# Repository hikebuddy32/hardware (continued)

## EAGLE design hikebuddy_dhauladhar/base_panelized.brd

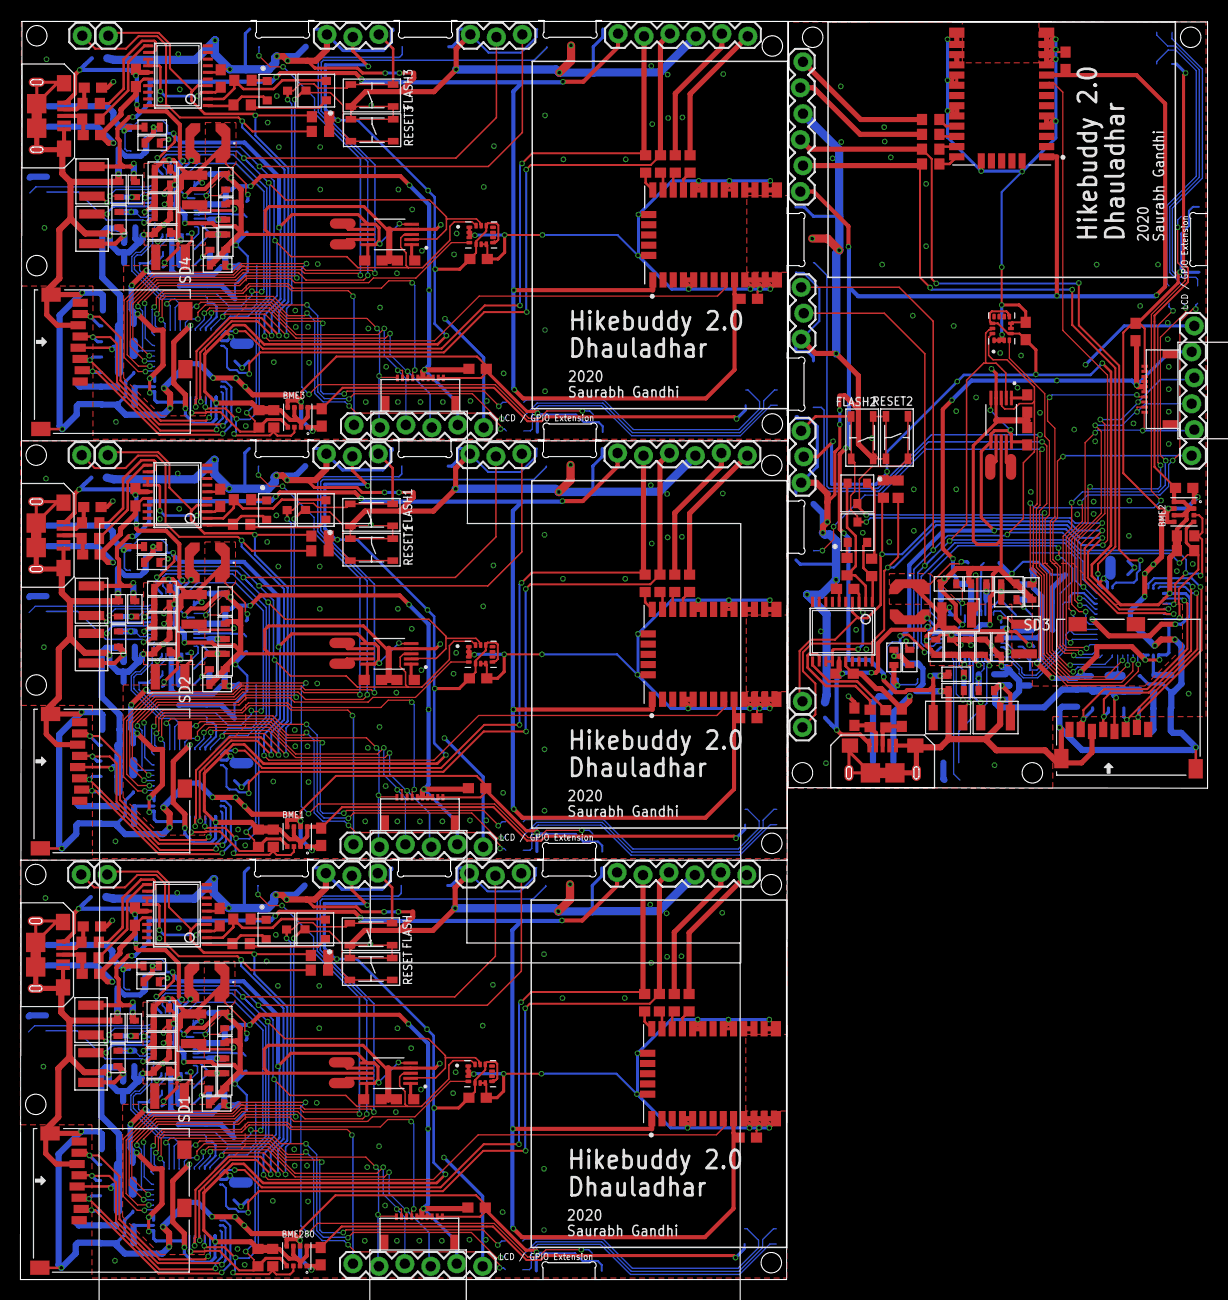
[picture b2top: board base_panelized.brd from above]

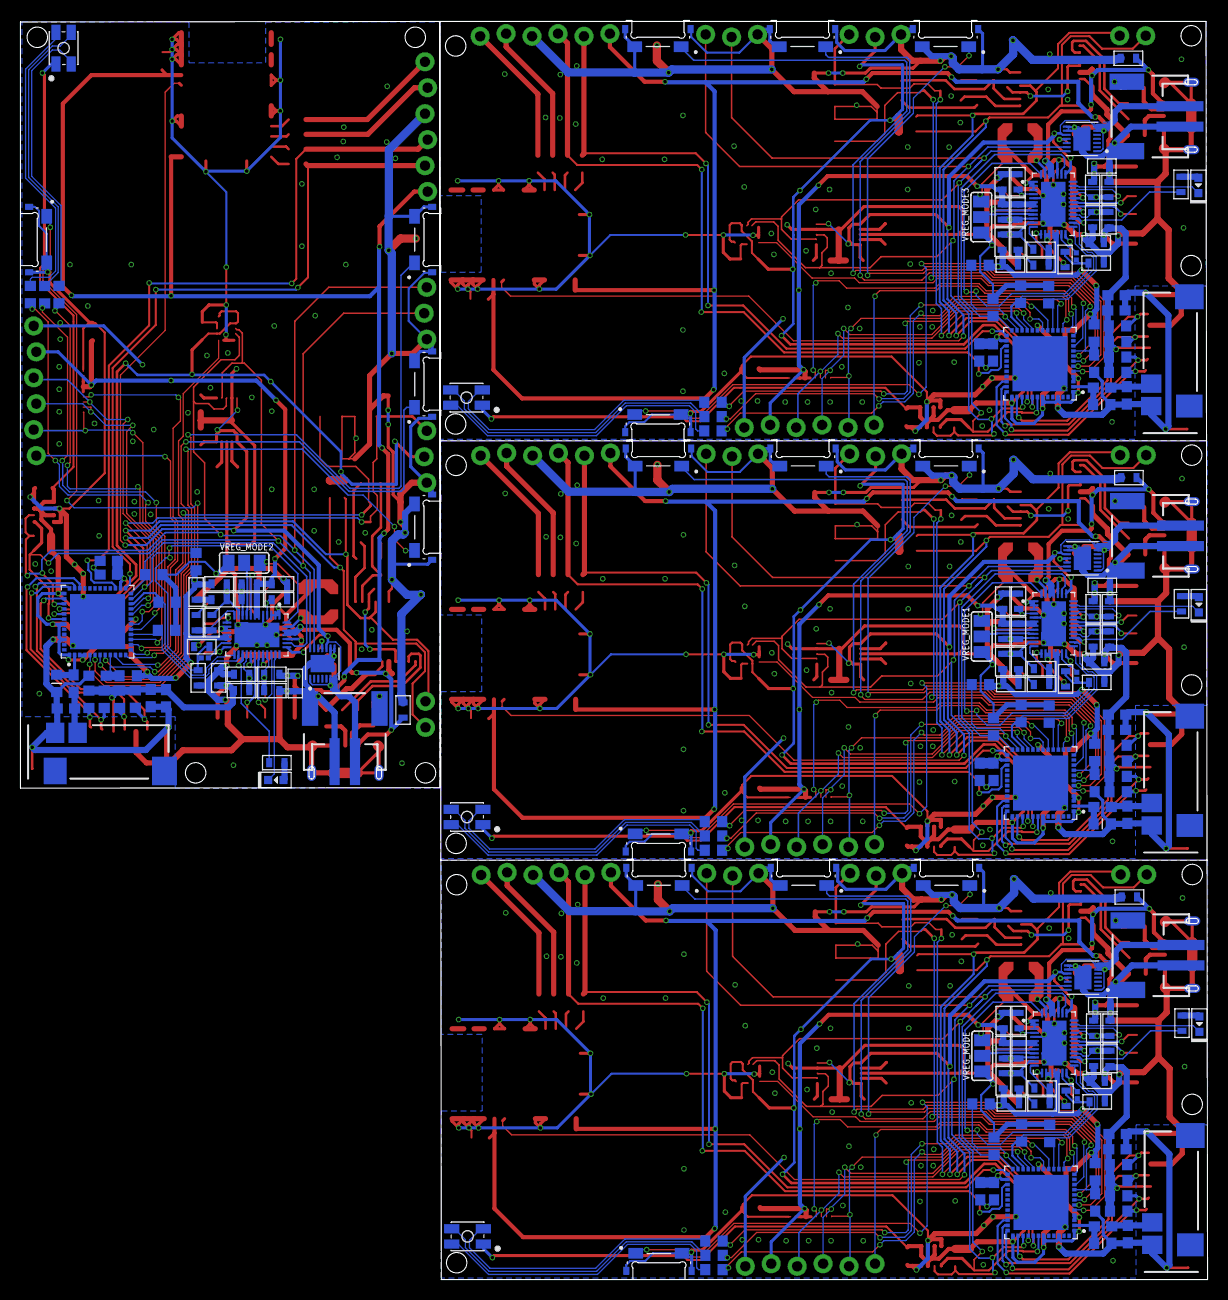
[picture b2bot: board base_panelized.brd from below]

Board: 2 copper layers, 116.2 x 123.2 mm, 456 parts (212 on the bottom side), 324 nets.

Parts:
ANT, ANT1, ANT2, ANT3: PRO-OB-440; PRO-OB-440_1
BATTERY1, BATTERY2, BATTERY3, BATTERY4: S2B-PH-SM4-TB(LF)(SN); JST-2-SMD
BME1, BME2, BME3, BME280: BME280; PSON65P250X250X100-8N
C1, C2, C22, C39, C75, C76, C112, C113: 4.7pF; C0603
C3, C4, C10, C14, C15, C20, C35, C40, C41, C45, C46, C49, C66, C73, C77, C78, C82, C83, C86, C103, C110, C114, C115, C119, C120, C123, C140, C147: 0.1uF; C0603
C5, C6, C42, C43, C79, C80, C116, C117: 47pF; C0603
C7, C8, C9, C16, C21, C23, C24, C27, C28, C38, C44, C47, C48, C53, C55, C58, C59, C71, C72, C74, C81, C84, C85, C90, C92, C95, C96, C108, C109, C111, C118, C121, C122, C127, C129, C132, C133, C145, C146, C148: 10uF; C0603
C11, C12, C29, C30, C50, C51, C60, C61, C87, C88, C97, C98, C124, C125, C134, C135: 22uF; C0603
C13, C18, C33, C52, C54, C64, C89, C91, C101, C126, C128, C138: 10pF; C0603
C17, C19, C36, C37, C67, C68, C69, C70, C104, C105, C106, C107, C141, C142, C143, C144: 4.7uF; C0603
C25, C26, C56, C57, C93, C94, C130, C131: 1uF; C0603
C31, C62, C99, C136: 33pF; C0603
C32, C63, C100, C137: 330pF; C0603
C34, C65, C102, C139: 0.47uF; C0603
D1, D3, D6, D8: MF-LED-0603-RED; LED0603
D2, D4, D5, D7: MF-LED-3228-RGB; PLCC4
ESP32-PICO-D1, ESP32-PICO-D2, ESP32-PICO-D3, ESP32-PICO-D4: ESP32-PICO-D4; PQFN50P700X700X104-49N
FLASH, FLASH1, FLASH2, FLASH3: MF-SW-TACT-4.2MM; TACT4.2MM
FT1, FT2, FT3, FT231: FT231XS; TSSOP20
J1, J10, J18, J26: MF-CON-MICROUSB-RIGHT; MICROUSB-RIGHT
J2, J9, J17, J25: GPS Port; 1X06_LOCK
J3, J4, J11, J12, J19, J20, J27, J28: 1X03_LOCK
J5, J13, J21, J29: SOLDER_PAD_2
J6, J7, J14, J15, J22, J23, J30, J31: 1X01
J8, J16, J24, J32: 1X06_LOCK
L1, L7, L13, L19: 30Ω/1.8A; L0603
L2, L8, L14, L20: 3.3uH; INDP_LPS4018-472MRB
L3, L5, L9, L11, L15, L17, L21, L23: 2.2uH; L1210
L4, L6, L10, L12, L16, L18, L22, L24: 4.7uH; L1210
R1, R2, R5, R6, R12, R13, R14, R30, R31, R32, R33, R36, R39, R43, R44, R47, R48, R49, R53, R73, R74, R75, R77, R78, R81, R82, R85, R86, R87, R91, R111, R112, R113, R115, R116, R119, R120, R123, R124, R125, R129, R149, R150, R151: 10k; R0603
R3, R4, R34, R35, R79, R80, R117, R118: 27; R0603
R7, R37, R38, R54, R55, R60, R92, R93, R98, R130, R131, R136: 2K; R0603
R8, R61, R99, R137: 3K; R0603
R9, R62, R100, R138: 560K; R0603
R10, R11, R40, R41, R42, R45, R46, R50, R51, R52, R83, R84, R88, R89, R90, R121, R122, R126, R127, R128: 1k; R0603
R15, R17, R18, R19, R56, R57, R58, R59, R94, R95, R96, R97, R132, R133, R134, R135: 100; R0603
R16, R21, R64, R76, R102, R114, R140, R152: 1K; R0603
R20, R63, R101, R139: 100K; R0603
R22, R24, R27, R65, R67, R70, R103, R105, R108, R141, R143, R146: 220K; R0603
R23, R25, R26, R66, R68, R69, R104, R106, R107, R142, R144, R145: 680K; R0603
R28, R71, R109, R147: 121K; R0603
R29, R72, R110, R148: 15K; R0603
RESET, RESET1, RESET2, RESET3: MF-SW-TACT-4.2MM; TACT4.2MM
S1, S2, S3, S4, S5, S6, S7, S8, S9, S10, S11, S12, S13, S14, S15, S16: EVQ-P4HB3B; SW_EVQ-P4HB3B
SD1, SD2, SD3, SD4: MF-MICROSD
TP1, TP2, TP3, TP4, TP5, TP6, TP7, TP8: TEST-POINT2; PAD.02X.02
U1, U9, U15, U21: LTC3586EUFE-1#PBF; QFN40P600X400X80-39N
U2, U10, U16, U22: MAX17260SETD+; SON40P300X300X80-15N
U3, U4, U7, U8, U13, U14, U19, U20: MF-DSC-SOT233-MMBT3904; SOT-23-3
U5, U11, U17, U23: DRV2605LTDGSRQ1; SOP50P490X110-10N
U6, U12, U18, U24: BMX160; PQFN50P250X300X100-14N
U$1, U$2, U$3, U$5: 51441-1093; FH12-10S-0.5SH
UBLOX_GPS, UBLOX_GPS1, UBLOX_GPS2, UBLOX_GPS3: CAM-M8C-0; LCC100P960X1400X210-31N
VREG_MODE, VREG_MODE1, VREG_MODE2, VREG_MODE3: VREG MODE; SJ_2

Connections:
3V3_GPS: C13.P$1, C16.P$2, C17.1, J2.6, L4.P$1, R23.P$1, UBLOX_GPS.1, UBLOX_GPS.9
3V3_GPS1: C52.P$1, C53.P$2, C69.1, J9.6, L10.P$1, R66.P$1, UBLOX_GPS1.1, UBLOX_GPS1.9
3V3_GPS2: C89.P$1, C90.P$2, C106.1, J17.6, L16.P$1, R104.P$1, UBLOX_GPS2.1, UBLOX_GPS2.9
3V3_GPS3: C126.P$1, C127.P$2, C143.1, J25.6, L22.P$1, R142.P$1, UBLOX_GPS3.1, UBLOX_GPS3.9
3V3_SDC: C14.1, C15.1, C18.P$1, C24.P$1, L6.P$2, R12.2, R13.2, R14.2, R25.P$1, R43.2, SD1.PIN4
3V3_SDC1: C45.1, C46.1, C54.P$1, C55.P$1, L12.P$2, R47.2, R48.2, R49.2, R53.2, R68.P$1, SD2.PIN4
3V3_SDC2: C82.1, C83.1, C91.P$1, C92.P$1, L18.P$2, R85.2, R86.2, R87.2, R91.2, R106.P$1, SD3.PIN4
3V3_SDC3: C119.1, C120.1, C128.P$1, C129.P$1, L24.P$2, R123.2, R124.2, R125.2, R129.2, R144.P$1, SD4.PIN4
BMX_INT: ESP32-PICO-D4.10, U6.4
BMX_INT1: ESP32-PICO-D1.10, U12.4
BMX_INT2: ESP32-PICO-D2.10, U18.4
BMX_INT3: ESP32-PICO-D3.10, U24.4
D+: C6.1, J1.3, R4.1
D+1: C43.1, J10.3, R35.1
D+2: C80.1, J18.3, R80.1
D+3: C117.1, J26.3, R118.1
D-: C5.1, J1.2, R3.1
D-1: C42.1, J10.2, R34.1
D-2: C79.1, J18.2, R79.1
D-3: C116.1, J26.2, R117.1
EN_GPS: ESP32-PICO-D4.16, R31.2, U1.21
EN_GPS1: ESP32-PICO-D1.16, R74.2, U9.21
EN_GPS2: ESP32-PICO-D2.16, R112.2, U15.21
EN_GPS3: ESP32-PICO-D3.16, R150.2, U21.21
EN_LCD: ESP32-PICO-D4.24, R36.2, U1.33
EN_LCD1: ESP32-PICO-D1.24, R75.2, U9.33
EN_LCD2: ESP32-PICO-D2.24, R113.2, U15.33
EN_LCD3: ESP32-PICO-D3.24, R151.2, U21.33
EN_SDC: ESP32-PICO-D4.22, R30.2, U1.20
EN_SDC1: ESP32-PICO-D1.22, R73.2, U9.20
EN_SDC2: ESP32-PICO-D2.22, R111.2, U15.20
EN_SDC3: ESP32-PICO-D3.22, R149.2, U21.20
ESP_EN: C3.2, ESP32-PICO-D4.9, R1.1, RESET.P$1, RESET.P$2, U4.P$3
ESP_EN1: C40.2, ESP32-PICO-D1.9, R32.1, RESET1.P$1, RESET1.P$2, U8.P$3
ESP_EN2: C77.2, ESP32-PICO-D2.9, R77.1, RESET2.P$1, RESET2.P$2, U14.P$3
ESP_EN3: C114.2, ESP32-PICO-D3.9, R115.1, RESET3.P$1, RESET3.P$2, U20.P$3
ESP_FLASH: ESP32-PICO-D4.23, FLASH.P$1, FLASH.P$2, J4.3, R2.1, U3.P$3
ESP_FLASH1: ESP32-PICO-D1.23, FLASH1.P$1, FLASH1.P$2, J12.3, R33.1, U7.P$3
ESP_FLASH2: ESP32-PICO-D2.23, FLASH2.P$1, FLASH2.P$2, J20.3, R78.1, U13.P$3
ESP_FLASH3: ESP32-PICO-D3.23, FLASH3.P$1, FLASH3.P$2, J28.3, R116.1, U19.P$3
ESP_RX: ESP32-PICO-D4.40, FT231.20, J6.1, R11.1
ESP_RX1: ESP32-PICO-D1.40, FT1.20, J14.1, R46.1
ESP_RX2: ESP32-PICO-D2.40, FT2.20, J22.1, R84.1
ESP_RX3: ESP32-PICO-D3.40, FT3.20, J30.1, R122.1
ESP_TX: ESP32-PICO-D4.41, FT231.4, J7.1, R10.1
ESP_TX1: ESP32-PICO-D1.41, FT1.4, J15.1, R45.1
ESP_TX2: ESP32-PICO-D2.41, FT2.4, J23.1, R83.1
ESP_TX3: ESP32-PICO-D3.41, FT3.4, J31.1, R121.1
GND: ANT.1, BATTERY1.1, BATTERY1.NC1, BATTERY1.NC2, BME280.1, BME280.5, BME280.7, C2.1, C3.1, C4.2, C5.2, C6.2, C7.2, C8.1, C9.P$2, C10.P$1, C12.P$1, C14.2, C15.2, C16.P$1, C17.2, C19.1, C20.P$1, C21.2, C23.2, C24.P$2, C25.P$1, C26.P$1, C27.P$1, C28.P$1, C29.P$1, C30.P$2, C34.P$1, C35.P$1, C36.2, C37.1, C38.1, ESP32-PICO-D4.49, FLASH.P$3, FLASH.P$4, FT231.6, FT231.16, J1.5, J1.S1, J1.S2, J1.S3, J1.S4, J1.S5, J1.S6, J2.3, J3.1, J4.1, J8.1, L1.2, R7.P$1, R8.P$1, R20.P$1, R22.P$2, R24.P$2, R27.P$1, R30.1, R31.1, R36.1, RESET.P$3, RESET.P$4, S1.2, S1.3, S1.4, S2.2, S2.3, S2.4, S3.2, S3.3, S3.4, S4.2, S4.3, S4.4, SD1.G0, SD1.G1, SD1.PIN6, U1.5, U1.39, U2.8, U2.9, U2.15, U5.4, U5.8, U6.1, U6.2, U6.3, U6.6, U6.7, U$5.VSS, U$5.VSSA, UBLOX_GPS.4, UBLOX_GPS.5, UBLOX_GPS.10, UBLOX_GPS.11, UBLOX_GPS.12, UBLOX_GPS.13, UBLOX_GPS.14, UBLOX_GPS.15, UBLOX_GPS.18, UBLOX_GPS.19, UBLOX_GPS.21, UBLOX_GPS.22, UBLOX_GPS.27, UBLOX_GPS.31, VREG_MODE.1
GND1: ANT1.1, BATTERY2.1, BATTERY2.NC1, BATTERY2.NC2, BME1.1, BME1.5, BME1.7, C39.1, C40.1, C41.2, C42.2, C43.2, C44.2, C45.2, C46.2, C47.2, C48.P$2, C49.P$1, C51.P$1, C53.P$1, C55.P$2, C56.P$1, C57.P$1, C58.P$1, C59.P$1, C60.P$1, C61.P$2, C65.P$1, C66.P$1, C67.2, C68.1, C69.2, C70.1, C71.1, C72.1, C73.P$1, C74.2, ESP32-PICO-D1.49, FLASH1.P$3, FLASH1.P$4, FT1.6, FT1.16, J9.3, J10.5, J10.S1, J10.S2, J10.S3, J10.S4, J10.S5, J10.S6, J11.1, J12.1, J16.1, L7.2, R60.P$1, R61.P$1, R63.P$1, R65.P$2, R67.P$2, R70.P$1, R73.1, R74.1, R75.1, RESET1.P$3, RESET1.P$4, S5.2, S5.3, S5.4, S6.2, S6.3, S6.4, S7.2, S7.3, S7.4, S8.2, S8.3, S8.4, SD2.G0, SD2.G1, SD2.PIN6, U9.5, U9.39, U10.8, U10.9, U10.15, U11.4, U11.8, U12.1, U12.2, U12.3, U12.6, U12.7, U$1.VSS, U$1.VSSA, UBLOX_GPS1.4, UBLOX_GPS1.5, UBLOX_GPS1.10, UBLOX_GPS1.11, UBLOX_GPS1.12, UBLOX_GPS1.13, UBLOX_GPS1.14, UBLOX_GPS1.15, UBLOX_GPS1.18, UBLOX_GPS1.19, UBLOX_GPS1.21, UBLOX_GPS1.22, UBLOX_GPS1.27, UBLOX_GPS1.31, VREG_MODE1.1
GND2: ANT3.1, BATTERY4.1, BATTERY4.NC1, BATTERY4.NC2, BME3.1, BME3.5, BME3.7, C113.1, C114.1, C115.2, C116.2, C117.2, C118.2, C119.2, C120.2, C121.2, C122.P$2, C123.P$1, C125.P$1, C127.P$1, C129.P$2, C130.P$1, C131.P$1, C132.P$1, C133.P$1, C134.P$1, C135.P$2, C139.P$1, C140.P$1, C141.2, C142.1, C143.2, C144.1, C145.1, C146.1, C147.P$1, C148.2, ESP32-PICO-D3.49, FLASH3.P$3, FLASH3.P$4, FT3.6, FT3.16, J25.3, J26.5, J26.S1, J26.S2, J26.S3, J26.S4, J26.S5, J26.S6, J27.1, J28.1, J32.1, L19.2, R136.P$1, R137.P$1, R139.P$1, R141.P$2, R143.P$2, R146.P$1, R149.1, R150.1, R151.1, RESET3.P$3, RESET3.P$4, S13.2, S13.3, S13.4, S14.2, S14.3, S14.4, S15.2, S15.3, S15.4, S16.2, S16.3, S16.4, SD4.G0, SD4.G1, SD4.PIN6, U21.5, U21.39, U22.8, U22.9, U22.15, U23.4, U23.8, U24.1, U24.2, U24.3, U24.6, U24.7, U$3.VSS, U$3.VSSA, UBLOX_GPS3.4, UBLOX_GPS3.5, UBLOX_GPS3.10, UBLOX_GPS3.11, UBLOX_GPS3.12, UBLOX_GPS3.13, UBLOX_GPS3.14, UBLOX_GPS3.15, UBLOX_GPS3.18, UBLOX_GPS3.19, UBLOX_GPS3.21, UBLOX_GPS3.22, UBLOX_GPS3.27, UBLOX_GPS3.31, VREG_MODE3.1
GND3: ANT2.1, BATTERY3.1, BATTERY3.NC1, BATTERY3.NC2, BME2.1, BME2.5, BME2.7, C76.1, C77.1, C78.2, C79.2, C80.2, C81.2, C82.2, C83.2, C84.2, C85.P$2, C86.P$1, C88.P$1, C90.P$1, C92.P$2, C93.P$1, C94.P$1, C95.P$1, C96.P$1, C97.P$1, C98.P$2, C102.P$1, C103.P$1, C104.2, C105.1, C106.2, C107.1, C108.1, C109.1, C110.P$1, C111.2, ESP32-PICO-D2.49, FLASH2.P$3, FLASH2.P$4, FT2.6, FT2.16, J17.3, J18.5, J18.S1, J18.S2, J18.S3, J18.S4, J18.S5, J18.S6, J19.1, J20.1, J24.1, L13.2, R98.P$1, R99.P$1, R101.P$1, R103.P$2, R105.P$2, R108.P$1, R111.1, R112.1, R113.1, RESET2.P$3, RESET2.P$4, S9.2, S9.3, S9.4, S10.2, S10.3, S10.4, S11.2, S11.3, S11.4, S12.2, S12.3, S12.4, SD3.G0, SD3.G1, SD3.PIN6, U15.5, U15.39, U16.8, U16.9, U16.15, U17.4, U17.8, U18.1, U18.2, U18.3, U18.6, U18.7, U$2.VSS, U$2.VSSA, UBLOX_GPS2.4, UBLOX_GPS2.5, UBLOX_GPS2.10, UBLOX_GPS2.11, UBLOX_GPS2.12, UBLOX_GPS2.13, UBLOX_GPS2.14, UBLOX_GPS2.15, UBLOX_GPS2.18, UBLOX_GPS2.19, UBLOX_GPS2.21, UBLOX_GPS2.22, UBLOX_GPS2.27, UBLOX_GPS2.31, VREG_MODE2.1
GPIO_EXT: ESP32-PICO-D4.13, J8.6
GPIO_EXT1: ESP32-PICO-D1.13, J16.6
GPIO_EXT2: ESP32-PICO-D2.13, J24.6
GPIO_EXT3: ESP32-PICO-D3.13, J32.6
GPS_RESET: J2.1, R18.2
GPS_RESET1: J9.1, R58.2
GPS_RESET2: J17.1, R96.2
GPS_RESET3: J25.1, R134.2
GPS_RX: ESP32-PICO-D4.25, J2.5, R17.2
GPS_RX1: ESP32-PICO-D1.25, J9.5, R57.2
GPS_RX2: ESP32-PICO-D2.25, J17.5, R95.2
GPS_RX3: ESP32-PICO-D3.25, J25.5, R133.2
GPS_SAFEBOOT: J2.2, R19.2
GPS_SAFEBOOT1: J9.2, R59.2
GPS_SAFEBOOT2: J17.2, R97.2
GPS_SAFEBOOT3: J25.2, R135.2
GPS_TX: ESP32-PICO-D4.27, J2.4, R15.1
GPS_TX1: ESP32-PICO-D1.27, J9.4, R56.1
GPS_TX2: ESP32-PICO-D2.27, J17.4, R94.1
GPS_TX3: ESP32-PICO-D3.27, J25.4, R132.1
I2C_SCL: BME280.4, ESP32-PICO-D4.42, J3.2, R37.1, U2.14, U5.2, U6.13
I2C_SCL1: BME1.4, ESP32-PICO-D1.42, J11.2, R54.1, U10.14, U11.2, U12.13
I2C_SCL2: BME2.4, ESP32-PICO-D2.42, J19.2, R92.1, U16.14, U17.2, U18.13
I2C_SCL3: BME3.4, ESP32-PICO-D3.42, J27.2, R130.1, U22.14, U23.2, U24.13
I2C_SDA: BME280.3, ESP32-PICO-D4.39, J3.3, R38.1, U2.13, U5.3, U6.14
I2C_SDA1: BME1.3, ESP32-PICO-D1.39, J11.3, R55.1, U10.13, U11.3, U12.14
I2C_SDA2: BME2.3, ESP32-PICO-D2.39, J19.3, R93.1, U16.13, U17.3, U18.14
I2C_SDA3: BME3.3, ESP32-PICO-D3.39, J27.3, R131.1, U22.13, U23.3, U24.14
JUMPER: U1.9, VREG_MODE.2
JUMPER1: U9.9, VREG_MODE1.2
JUMPER2: U15.9, VREG_MODE2.2
JUMPER3: U21.9, VREG_MODE3.2
LCD_CLK: ESP32-PICO-D4.17, J8.5, U$5.SCLK
LCD_CLK1: ESP32-PICO-D1.17, J16.5, U$1.SCLK
LCD_CLK2: ESP32-PICO-D2.17, J24.5, U$2.SCLK
LCD_CLK3: ESP32-PICO-D3.17, J32.5, U$3.SCLK
LCD_CS: ESP32-PICO-D4.21, J8.3, U$5.SCS
LCD_CS1: ESP32-PICO-D1.21, J16.3, U$1.SCS
LCD_CS2: ESP32-PICO-D2.21, J24.3, U$2.SCS
LCD_CS3: ESP32-PICO-D3.21, J32.3, U$3.SCS
LCD_EXTCOMM: ESP32-PICO-D4.12, U$5.EXTCOMIN
LCD_EXTCOMM1: ESP32-PICO-D1.12, U$1.EXTCOMIN
LCD_EXTCOMM2: ESP32-PICO-D2.12, U$2.EXTCOMIN
LCD_EXTCOMM3: ESP32-PICO-D3.12, U$3.EXTCOMIN
LCD_MOSI: ESP32-PICO-D4.20, J8.4, U$5.SI
LCD_MOSI1: ESP32-PICO-D1.20, J16.4, U$1.SI
LCD_MOSI2: ESP32-PICO-D2.20, J24.4, U$2.SI
LCD_MOSI3: ESP32-PICO-D3.20, J32.4, U$3.SI
LED1: ESP32-PICO-D4.18, R40.1
LED2: ESP32-PICO-D4.15, R41.1
LED3: ESP32-PICO-D4.14, R42.1
LED4: ESP32-PICO-D1.18, R50.1
LED5: ESP32-PICO-D1.15, R51.1
LED6: ESP32-PICO-D1.14, R52.1
LED7: ESP32-PICO-D2.18, R88.1
LED8: ESP32-PICO-D2.15, R89.1
LED9: ESP32-PICO-D2.14, R90.1
LED10: ESP32-PICO-D3.18, R126.1
LED11: ESP32-PICO-D3.15, R127.1
LED12: ESP32-PICO-D3.14, R128.1
unnamed: C1.1, ESP32-PICO-D4.2, L1.1
unnamed: ANT.2, C1.2, C2.2
unnamed: R5.2, U3.P$1
unnamed: R6.2, U4.P$1
unnamed: C4.1, FT231.3, FT231.13, FT231.14
unnamed: FT231.12, R3.2
unnamed: FT231.11, R4.2
unnamed: FT231.2, R5.1, U4.P$2
unnamed: FT231.1, R6.1, U3.P$2
unnamed: R7.P$2, U1.29
unnamed: C10.P$2, R8.P$2, U1.4
unnamed: C11.P$1, R9.P$1, R20.P$2, U1.10
unnamed: L3.P$2, U1.13
unnamed: C31.P$1, C32.P$1, C33.P$1, R26.P$1, R27.P$2, U1.11
unnamed: L2.2, U1.37
unnamed: D1.CATHODE, U1.30
unnamed: D1.ANODE, R21.P$1
unnamed: L3.P$1, U1.19
unnamed: TP2.P$1, U1.18
unnamed: L4.P$2, U1.26
unnamed: C13.P$2, R22.P$1, R23.P$2, U1.28
unnamed: L5.P$1, U1.8
unnamed: C22.1, ESP32-PICO-D1.2, L7.1
unnamed: C20.P$2, R16.P$2, TP1.P$1, U1.38
unnamed: ANT1.2, C22.2, C39.2
unnamed: C18.P$2, R24.P$1, R25.P$2, U1.23
unnamed: L6.P$1, U1.25
unnamed: D4.P$2, R40.2
unnamed: R15.2, UBLOX_GPS.25
unnamed: R17.1, UBLOX_GPS.26
unnamed: C31.P$2, R28.P$1
unnamed: D4.P$3, R42.2
unnamed: D4.P$4, R41.2
unnamed: UBLOX_GPS.16, UBLOX_GPS.17
unnamed: C41.1, FT1.3, FT1.13, FT1.14
unnamed: FT1.12, R34.2
unnamed: R18.1, UBLOX_GPS.23
unnamed: R19.1, UBLOX_GPS.24
unnamed: FT1.11, R35.2
unnamed: R39.2, U7.P$1
unnamed: C36.1, U5.1
unnamed: R44.2, U8.P$1
unnamed: C33.P$2, R29.P$2, U1.12
unnamed: C32.P$2, R29.P$1
unnamed: FT1.2, R39.1, U8.P$2
unnamed: FT1.1, R44.1, U7.P$2
unnamed: C34.P$2, U2.11
unnamed: D2.P$2, R50.2
unnamed: D2.P$4, R51.2
unnamed: J5.P$2, U5.9
unnamed: J5.P$1, U5.7
unnamed: D2.P$3, R52.2
unnamed: R56.2, UBLOX_GPS1.25
unnamed: R57.1, UBLOX_GPS1.26
unnamed: UBLOX_GPS1.16, UBLOX_GPS1.17
unnamed: R58.1, UBLOX_GPS1.23
unnamed: R59.1, UBLOX_GPS1.24
unnamed: R60.P$2, U9.29
unnamed: C49.P$2, R61.P$2, U9.4
unnamed: L8.2, U9.37
unnamed: D3.CATHODE, U9.30
unnamed: D3.ANODE, R64.P$1
unnamed: L9.P$2, U9.13
unnamed: L9.P$1, U9.19
unnamed: L10.P$2, U9.26
unnamed: C52.P$2, R65.P$1, R66.P$2, U9.28
unnamed: C54.P$2, R67.P$1, R68.P$2, U9.23
unnamed: L12.P$1, U9.25
unnamed: L11.P$1, U9.8
unnamed: C50.P$1, R62.P$1, R63.P$2, U9.10
unnamed: C62.P$1, C63.P$1, C64.P$1, R69.P$1, R70.P$2, U9.11
unnamed: C62.P$2, R71.P$1
unnamed: C64.P$2, R72.P$2, U9.12
unnamed: C63.P$2, R72.P$1
unnamed: C65.P$2, U10.11
unnamed: C67.1, U11.1
unnamed: J13.P$2, U11.9
unnamed: J13.P$1, U11.7
unnamed: C73.P$2, R76.P$2, TP3.P$1, U9.38
unnamed: TP4.P$1, U9.18
unnamed: C75.1, ESP32-PICO-D2.2, L13.1
unnamed: ANT2.2, C75.2, C76.2
unnamed: C78.1, FT2.3, FT2.13, FT2.14
unnamed: FT2.12, R79.2
unnamed: FT2.11, R80.2
unnamed: R81.2, U13.P$1
unnamed: R82.2, U14.P$1
unnamed: FT2.2, R81.1, U14.P$2
unnamed: FT2.1, R82.1, U13.P$2
unnamed: D5.P$2, R88.2
unnamed: D5.P$4, R89.2
unnamed: D5.P$3, R90.2
unnamed: R94.2, UBLOX_GPS2.25
unnamed: R95.1, UBLOX_GPS2.26
unnamed: UBLOX_GPS2.16, UBLOX_GPS2.17
unnamed: R96.1, UBLOX_GPS2.23
unnamed: R97.1, UBLOX_GPS2.24
unnamed: R98.P$2, U15.29
unnamed: C86.P$2, R99.P$2, U15.4
unnamed: L14.2, U15.37
unnamed: D6.CATHODE, U15.30
unnamed: D6.ANODE, R102.P$1
unnamed: L15.P$2, U15.13
unnamed: L15.P$1, U15.19
unnamed: L16.P$2, U15.26
unnamed: C89.P$2, R103.P$1, R104.P$2, U15.28
unnamed: C91.P$2, R105.P$1, R106.P$2, U15.23
unnamed: L18.P$1, U15.25
unnamed: L17.P$1, U15.8
unnamed: C87.P$1, R100.P$1, R101.P$2, U15.10
unnamed: C99.P$1, C100.P$1, C101.P$1, R107.P$1, R108.P$2, U15.11
unnamed: C99.P$2, R109.P$1
unnamed: C101.P$2, R110.P$2, U15.12
unnamed: C100.P$2, R110.P$1
unnamed: C102.P$2, U16.11
unnamed: C104.1, U17.1
unnamed: J21.P$2, U17.9
unnamed: J21.P$1, U17.7
unnamed: C110.P$2, R114.P$2, TP5.P$1, U15.38
unnamed: TP6.P$1, U15.18
unnamed: C112.1, ESP32-PICO-D3.2, L19.1
unnamed: ANT3.2, C112.2, C113.2
unnamed: C115.1, FT3.3, FT3.13, FT3.14
unnamed: FT3.12, R117.2
unnamed: FT3.11, R118.2
unnamed: R119.2, U19.P$1
unnamed: R120.2, U20.P$1
unnamed: FT3.2, R119.1, U20.P$2
unnamed: FT3.1, R120.1, U19.P$2
unnamed: D7.P$2, R126.2
unnamed: D7.P$4, R127.2
unnamed: D7.P$3, R128.2
unnamed: R132.2, UBLOX_GPS3.25
unnamed: R133.1, UBLOX_GPS3.26
unnamed: UBLOX_GPS3.16, UBLOX_GPS3.17
unnamed: R134.1, UBLOX_GPS3.23
unnamed: R135.1, UBLOX_GPS3.24
unnamed: R136.P$2, U21.29
unnamed: C123.P$2, R137.P$2, U21.4
unnamed: L20.2, U21.37
unnamed: D8.CATHODE, U21.30
unnamed: D8.ANODE, R140.P$1
unnamed: L21.P$2, U21.13
unnamed: L21.P$1, U21.19
unnamed: L22.P$2, U21.26
unnamed: C126.P$2, R141.P$1, R142.P$2, U21.28
unnamed: C128.P$2, R143.P$1, R144.P$2, U21.23
unnamed: L24.P$1, U21.25
unnamed: L23.P$1, U21.8
unnamed: C124.P$1, R138.P$1, R139.P$2, U21.10
unnamed: C136.P$1, C137.P$1, C138.P$1, R145.P$1, R146.P$2, U21.11
unnamed: C136.P$2, R147.P$1
unnamed: C138.P$2, R148.P$2, U21.12
unnamed: C137.P$2, R148.P$1
unnamed: C139.P$2, U22.11
unnamed: C141.1, U23.1
unnamed: J29.P$2, U23.9
unnamed: J29.P$1, U23.7
unnamed: C147.P$2, R152.P$2, TP7.P$1, U21.38
unnamed: TP8.P$1, U21.18
SD_CLK: ESP32-PICO-D4.35, R14.1, SD1.PIN5
SD_CLK1: ESP32-PICO-D1.35, R49.1, SD2.PIN5
SD_CLK2: ESP32-PICO-D2.35, R87.1, SD3.PIN5
SD_CLK3: ESP32-PICO-D3.35, R125.1, SD4.PIN5
SD_CS: ESP32-PICO-D4.34, R12.1, SD1.PIN2
SD_CS1: ESP32-PICO-D1.34, R47.1, SD2.PIN2
SD_CS2: ESP32-PICO-D2.34, R85.1, SD3.PIN2
SD_CS3: ESP32-PICO-D3.34, R123.1, SD4.PIN2
SD_MISO: ESP32-PICO-D4.38, R43.1, SD1.PIN7
SD_MISO1: ESP32-PICO-D1.38, R53.1, SD2.PIN7
SD_MISO2: ESP32-PICO-D2.38, R91.1, SD3.PIN7
SD_MISO3: ESP32-PICO-D3.38, R129.1, SD4.PIN7
SD_MOSI: ESP32-PICO-D4.36, R13.1, SD1.PIN3
SD_MOSI1: ESP32-PICO-D1.36, R48.1, SD2.PIN3
SD_MOSI2: ESP32-PICO-D2.36, R86.1, SD3.PIN3
SD_MOSI3: ESP32-PICO-D3.36, R124.1, SD4.PIN3
SW1: ESP32-PICO-D4.5, S1.1
SW2: ESP32-PICO-D4.6, S4.1
SW3: ESP32-PICO-D4.7, S3.1
SW4: ESP32-PICO-D4.8, S2.1
SW5: ESP32-PICO-D1.5, S8.1
SW6: ESP32-PICO-D1.6, S7.1
SW7: ESP32-PICO-D1.7, S6.1
SW8: ESP32-PICO-D1.8, S5.1
SW9: ESP32-PICO-D2.5, S12.1
SW10: ESP32-PICO-D2.6, S11.1
SW11: ESP32-PICO-D2.7, S10.1
SW12: ESP32-PICO-D2.8, S9.1
SW13: ESP32-PICO-D3.5, S16.1
SW14: ESP32-PICO-D3.6, S15.1
SW15: ESP32-PICO-D3.7, S14.1
SW16: ESP32-PICO-D3.8, S13.1
VCC: BME280.2, BME280.6, BME280.8, C8.2, C21.1, C23.1, C30.P$1, C38.2, D4.P$1, ESP32-PICO-D4.1, ESP32-PICO-D4.3, ESP32-PICO-D4.4, ESP32-PICO-D4.19, ESP32-PICO-D4.26, ESP32-PICO-D4.37, ESP32-PICO-D4.43, ESP32-PICO-D4.46, J4.2, R1.2, R2.2, R10.2, R11.2, R26.P$2, R28.P$2, R37.2, R38.2, U1.16, U1.17, U6.5, U6.8, U6.12
VCC1: BME1.2, BME1.6, BME1.8, C47.1, C61.P$1, C71.2, C72.2, C74.1, D2.P$1, ESP32-PICO-D1.1, ESP32-PICO-D1.3, ESP32-PICO-D1.4, ESP32-PICO-D1.19, ESP32-PICO-D1.26, ESP32-PICO-D1.37, ESP32-PICO-D1.43, ESP32-PICO-D1.46, J12.2, R32.2, R33.2, R45.2, R46.2, R54.2, R55.2, R69.P$2, R71.P$2, U9.16, U9.17, U12.5, U12.8, U12.12
VCC2: BME2.2, BME2.6, BME2.8, C84.1, C98.P$1, C108.2, C109.2, C111.1, D5.P$1, ESP32-PICO-D2.1, ESP32-PICO-D2.3, ESP32-PICO-D2.4, ESP32-PICO-D2.19, ESP32-PICO-D2.26, ESP32-PICO-D2.37, ESP32-PICO-D2.43, ESP32-PICO-D2.46, J20.2, R77.2, R78.2, R83.2, R84.2, R92.2, R93.2, R107.P$2, R109.P$2, U15.16, U15.17, U18.5, U18.8, U18.12
VCC3: BME3.2, BME3.6, BME3.8, C121.1, C135.P$1, C145.2, C146.2, C148.1, D7.P$1, ESP32-PICO-D3.1, ESP32-PICO-D3.3, ESP32-PICO-D3.4, ESP32-PICO-D3.19, ESP32-PICO-D3.26, ESP32-PICO-D3.37, ESP32-PICO-D3.43, ESP32-PICO-D3.46, J28.2, R115.2, R116.2, R121.2, R122.2, R130.2, R131.2, R145.P$2, R147.P$2, U21.16, U21.17, U24.5, U24.8, U24.12
V_BAT: BATTERY1.2, C35.P$2, C37.2, U1.32, U2.1, U2.6, U2.7, U2.10, U5.5, U5.6, U5.10, UBLOX_GPS.8
V_BAT1: BATTERY2.2, C66.P$2, C68.2, U9.32, U10.1, U10.6, U10.7, U10.10, U11.5, U11.6, U11.10, UBLOX_GPS1.8
V_BAT2: BATTERY3.2, C103.P$2, C105.2, U15.32, U16.1, U16.6, U16.7, U16.10, U17.5, U17.6, U17.10, UBLOX_GPS2.8
V_BAT3: BATTERY4.2, C140.P$2, C142.2, U21.32, U22.1, U22.6, U22.7, U22.10, U23.5, U23.6, U23.10, UBLOX_GPS3.8
V_LCD: C11.P$2, C19.2, C29.P$2, J8.2, R9.P$2, U1.6, U1.7, U$5.DISP, U$5.EXTMODE, U$5.VDD, U$5.VDDA
V_LCD1: C50.P$2, C60.P$2, C70.2, J16.2, R62.P$2, U9.6, U9.7, U$1.DISP, U$1.EXTMODE, U$1.VDD, U$1.VDDA
V_LCD2: C87.P$2, C97.P$2, C107.2, J24.2, R100.P$2, U15.6, U15.7, U$2.DISP, U$2.EXTMODE, U$2.VDD, U$2.VDDA
V_LCD3: C124.P$2, C134.P$2, C144.2, J32.2, R138.P$2, U21.6, U21.7, U$3.DISP, U$3.EXTMODE, U$3.VDD, U$3.VDDA
V_REG: C12.P$2, C25.P$2, C26.P$2, C27.P$2, C28.P$2, L2.1, L5.P$2, R16.P$1, R21.P$2, U1.1, U1.2, U1.3, U1.14, U1.15, U1.22, U1.24, U1.27, U1.34, VREG_MODE.3
V_REG1: C51.P$2, C56.P$2, C57.P$2, C58.P$2, C59.P$2, L8.1, L11.P$2, R64.P$2, R76.P$1, U9.1, U9.2, U9.3, U9.14, U9.15, U9.22, U9.24, U9.27, U9.34, VREG_MODE1.3
V_REG2: C88.P$2, C93.P$2, C94.P$2, C95.P$2, C96.P$2, L14.1, L17.P$2, R102.P$2, R114.P$1, U15.1, U15.2, U15.3, U15.14, U15.15, U15.22, U15.24, U15.27, U15.34, VREG_MODE2.3
V_REG3: C125.P$2, C130.P$2, C131.P$2, C132.P$2, C133.P$2, L20.1, L23.P$2, R140.P$2, R152.P$1, U21.1, U21.2, U21.3, U21.14, U21.15, U21.22, U21.24, U21.27, U21.34, VREG_MODE3.3
V_USB: C7.1, C9.P$1, FT231.15, J1.1, U1.35, U1.36
V_USB1: C44.1, C48.P$1, FT1.15, J10.1, U9.35, U9.36
V_USB2: C81.1, C85.P$1, FT2.15, J18.1, U15.35, U15.36
V_USB3: C118.1, C122.P$1, FT3.15, J26.1, U21.35, U21.36

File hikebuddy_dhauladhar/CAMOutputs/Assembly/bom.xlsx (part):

Qty | Value | Device | Package | Parts | Description | AVAILABILITY | DESCRIPTION.1 | DIELECTRIC | DNP | HEIGHT | HOUSEPART | MANUFACTURER_NAME | MANUFACTURER_PART_NUMBER | MF | MOUSER_PART_NUMBER | MOUSER_PRICE-STOCK | MP | MPN | PACKAGE.1 | POPULARITY | POPULATE | PRICE | PROD_ID | RS_PART_NUMBER | RS_PRICE-STOCK | SF_ID | SPICEPREFIX | TOLERANCE | URL | VALUE.1 | VOLTAGE | WATTAGE | Column1
2 |  | CONN_01 | 1X01 | J6, J7 | Single connection point. Often used as Generic Header-pin footprint for 0.1 inc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 |  |  |  | 1
2 |  | CONN_03LOCK | 1X03_LOCK | J3, J4 | Multi connection point. Often used as Generic Header-pin footprint for 0.1 inch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 |  |  |  | 1
1 |  | CONN_06LOCK | 1X06_LOCK | J8 | Multi connection point. Often used as Generic Header-pin footprint for 0.1 inch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 |  |  |  | 1
1 | LTC3586EUFE-1#PBF | LTC3586EUFE-3#TRPBF | QFN40P600X400X80-39N | U1 | None | Unavailable | USB Power Manager 4.35V to 5.5V 38-Pin QFN EP T/R |  |  |  |  |  |  | Analog Devices |  |  | LTC3586EUFE |  | QFN -38 Analog Devices |  |  | None
4 | 0.1uF | 0.1UF-0603-25V-(+80/-20%) | C0603 | C3, C4, C14, C15 | 0.1ÂµF ceramic capacitors |  |  |  |  |  |  |  |  |  |  |  |  |  |  |  |  |  | CAP-00810 |  |  |  |  |  |  | 0.1uF
3 | 0.1uF | CAPACITOR_NP_0603 | C0603 | C10, C20, C35 | Library: MF_Passives |  |  |  |  |  |  |  |  |  |  |  |  |  |  |  | 1
1 | 0.47uF | CAPACITOR_NP_0603 | C0603 | C34 | Library: MF_Passives |  |  |  |  |  |  |  |  |  |  |  |  |  |  |  | 1
2 | 100 | 1KOHM-0603-1/10W-1% | R0603 | R18, R19 | 1kÎ© resistor |  |  |  | 1 |  |  |  |  |  |  |  |  |  |  |  |  |  | RES-07856 |  |  |  |  |  |  | 1k
2 | 100 | 1KOHM-0603-1/10W-1% | R0603 | R15, R17 | 1kÎ© resistor |  |  |  |  |  |  |  |  |  |  |  |  |  |  |  |  |  | RES-07856 |  |  |  |  |  |  | 1k
1 | 100K | RESISTOR_0603 | R0603 | R20 | Library: MF_Passives |  |  |  |  |  |  |  |  |  |  |  |  |  |  |  | 1
11 | 10k | 10KOHM-0603-1/10W-1% | R0603 | R1, R2, R5, R6, R12, R13, R14, R30, R31, R36, R43 | 10kÎ© resistor |  |  |  |  |  |  |  |  |  |  |  |  |  |  |  |  |  | RES-00824 |  |  |  |  |  |  | 10k
3 | 10pF | CAPACITOR_NP_0603 | C0603 | C13, C18, C33 | Library: MF_Passives |  |  |  |  |  |  |  |  |  |  |  |  |  |  |  | 1
2 | 10uF | 10UF-0603-6.3V-20% | C0603 | C21, C23 | 10.0ÂµF ceramic capacitors |  |  |  |  |  |  |  |  |  |  |  |  |  |  |  |  |  | CAP-11015 |  |  |  |  |  |  | 10uF
1 | 10uF | 2.2UF-0603-10V-20% | C0603 | C7 | 2.2ÂµF ceramic capacitors |  |  |  |  |  |  |  |  |  |  |  |  |  |  |  |  |  | CAP-07888 |  |  |  |  |  |  | 2.2uF
2 | 10uF | 4.7PF-0603-50V-5% | C0603 | C8, C38 | 4.7pF ceramic capacitors |  |  |  |  |  |  |  |  |  |  |  |  |  |  |  |  |  | CAP-07880 |  |  |  |  |  |  | 4.7pF
5 | 10uF | CAPACITOR_NP_0603 | C0603 | C9, C16, C24, C27, C28 | Library: MF_Passives |  |  |  |  |  |  |  |  |  |  |  |  |  |  |  | 1
1 | 121K | RESISTOR_0603 | R0603 | R28 | Library: MF_Passives |  |  |  |  |  |  |  |  |  |  |  |  |  |  |  | 1
1 | 15K | RESISTOR_0603 | R0603 | R29 | Library: MF_Passives |  |  |  |  |  |  |  |  |  |  |  |  |  |  |  | 1
2 | 1K | RESISTOR_0603 | R0603 | R16, R21 | Library: MF_Passives |  |  |  |  |  |  |  |  |  |  |  |  |  |  |  | 1
5 | 1k | 1KOHM-0603-1/10W-1% | R0603 | R10, R11, R40, R41, R42 | 1kÎ© resistor |  |  |  |  |  |  |  |  |  |  |  |  |  |  |  |  |  | RES-07856 |  |  |  |  |  |  | 1k
2 | 1uF | CAPACITOR_NP_0603 | C0603 | C25, C26 | Library: MF_Passives |  |  |  |  |  |  |  |  |  |  |  |  |  |  |  | 1
2 | 2.2uH | INDUCTOR_1210 | L1210 | L3, L5 | Library: MF_Passives |  |  |  |  |  |  |  |  |  |  |  |  | L1210R2R2MDWIT
3 | 220K | RESISTOR_0603 | R0603 | R22, R24, R27 | Library: MF_Passives |  |  |  |  |  |  |  |  |  |  |  |  |  |  |  | 1
4 | 22uF | CAPACITOR_NP_0603 | C0603 | C11, C12, C29, C30 | Library: MF_Passives |  |  |  |  |  |  |  |  |  |  |  |  |  |  |  | 1
2 | 27 | 27OHM-0603-1/10W-1% | R0603 | R3, R4 | 27Î© resistor |  |  |  |  |  |  |  |  |  |  |  |  |  |  |  |  |  | RES-09334 |  |  |  |  |  |  | 27
2 | 2K | 1KOHM-0603-1/10W-1% | R0603 | R37, R38 | 1kÎ© resistor |  |  |  |  |  |  |  |  |  |  |  |  |  |  |  |  |  | RES-07856 |  |  |  |  |  |  | 1k
1 | 2K | RESISTOR_0603 | R0603 | R7 | Library: MF_Passives |  |  |  |  |  |  |  |  |  |  |  |  |  |  |  | 1
1 | 3.3uH | LPS4018-472MRB | INDP_LPS4018-472MRB | L2 | Power inductor, shielded, 20/30% tol, SMT, RoHS, lead-free, halogen-free | Unavailable | Power inductor, shielded, 20/30% tol, SMT, RoHS, lead-free, halogen-free |  |  |  |  |  |  | Coilcraft |  |  | LPS4018-472MRB | LPS4018-472MRB | None |  |  | None
1 | 30Î©/1.8A | FERRITE_BEAD-0603 | L0603 | L1 | Ferrite Bead (blocks, cores, rings, chokes, etc.) |  |  |  |  |  |  |  |  |  |  |  |  | 744761016C |  |  |  |  | NDUC-13805 |  |  |  |  |  |  | 30Î©/1.8A
1 | 330pF | CAPACITOR_NP_0603 | C0603 | C32 | Library: MF_Passives |  |  |  |  |  |  |  |  |  |  |  |  |  |  |  | 1
1 | 33pF | CAPACITOR_NP_0603 | C0603 | C31 | Library: MF_Passives |  |  |  |  |  |  |  |  |  |  |  |  |  |  |  | 1
1 | 3K | RESISTOR_0603 | R0603 | R8 | Library: MF_Passives |  |  |  |  |  |  |  |  |  |  |  |  |  |  |  | 1
2 | 4.7pF | 4.7PF-0603-50V-5% | C0603 | C1, C2 | 4.7pF ceramic capacitors |  |  |  |  |  |  |  |  |  |  |  |  |  |  |  |  |  | CAP-07880 |  |  |  |  |  |  | 4.7pF
1 | 4.7uF | 0.1UF-0603-25V-5% | C0603 | C17 | 0.1ÂµF ceramic capacitors |  |  |  |  |  |  |  |  |  |  |  |  |  |  |  |  |  | CAP-08604 |  |  |  |  |  |  | 0.1uF
3 | 4.7uF | 4.7UF-0603-6.3V-(10%) | C0603 | C19, C36, C37 | 4.7ÂµF ceramic capacitors |  |  |  |  |  |  |  |  |  |  |  |  |  |  |  |  |  | CAP-08280 |  |  |  |  |  |  | 4.7uF
2 | 4.7uH | INDUCTOR_1210 | L1210 | L4, L6 | Library: MF_Passives |  |  |  |  |  |  |  |  |  |  |  |  | L1210R4R7MDWIT
1 | 47352-1001 | 47352-1001 | MOLEX_47352-1001 | J9 | 1.10mm Pitch microSD Card Connector, Push-Push Type, with VSS (Supply Voltage G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 | Unavailable | 1.10mm Pitch microSD Card Connector, Push-Push Type, with VSS _Supply Voltage G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 |  |  |  |  |  |  | Molex |  |  | 47352-1001 |  | None |  |  | None
2 | 47pF | 47PF-0603-50V-5% | C0603 | C5, C6 | 47pF ceramic capacitors |  |  |  |  |  |  |  |  |  |  |  |  |  |  |  |  |  | CAP-08913 |  |  |  |  |  |  | 47pF
1 | 51441-1093 | LS027B_LCD_SHARPFH12-10S-0.5SH | FH12-10S-0.5SH | U$5 |  |  |  |  |  |  |  |  |  |  |  |  |  | 51441-1093
1 | 560K | RESISTOR_0603 | R0603 | R9 | Library: MF_Passives |  |  |  |  |  |  |  |  |  |  |  |  |  |  |  | 1
3 | 680K | RESISTOR_0603 | R0603 | R23, R25, R26 | Library: MF_Passives |  |  |  |  |  |  |  |  |  |  |  |  |  |  |  | 1
1 | BME280 | BME280 | PSON65P250X250X100-8N | BME280 | DIGITAL HUMIDITY, PRESSURE AND TEMPERATURE SENSOR* Digital interface IÂ²C (up t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 | Unavailable | Integrated pressure, humidity and temperature sensor | 8-pin 2.5x2.5x0.93mm LGA |  |  |  |  |  |  | Bosch |  |  | BME280 |  | LGA-8 Bosch |  |  | None
1 | BMX160 | BMX160 | PQFN50P250X300X100-14N | U6 | IMU ACCEL/GYRO/MAG | Unavailable | Accelerometer, Gyroscope, Magnetometer, 9 Axis Sensor IÂ²C, SPI Output |  |  |  |  |  |  | Bosch Sensortec |  |  | BMX160 |  | VFLGA-14 Bosch Sensortec |  |  | None
1 | CAM-M8C-0 | CAM-M8C-0 | LCC100P960X1400X210-31N | UBLOX_GPS | None | Unavailable | Ic Receiver Gps Chip Ant 31lcc |  |  |  |  |  |  | U-Blox America |  |  | CAM-M8C-0 |  | SMD-31 u-blox |  |  | None
1 | DRV2605LTDGSRQ1 | DRV2605LTDGSRQ1 | SOP50P490X110-10N | U5 | None | Unavailable | Haptic Driver for ERM and LRA With Built-In Library and Smart Loop A 10-VSSOP -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 |  |  |  |  |  |  | Texas Instruments |  |  | DRV2605LTDGSRQ1 |  | TFSOP-10 Texas Instruments |  |  | None
1 | ESP32-PICO-D4 | ESP32-PICO-D4 | PQFN50P700X700X104-49N | ESP32-PICO-D4 | The ESP32-PICO-D4 is a System-in-Package (SIP) module that is based on ESP32, p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 | Unavailable | WIFi/Bluetooth SIP |  |  |  |  |  |  | Espressif Systems |  |  | ESP32-PICO-D4 |  | SMD-48 Espressif Systems |  |  | None
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
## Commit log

2019-03-19 Hardware v1 files
2019-03-19 fixed gitignore
2019-03-19 added hardware reference files
2019-03-19 initial firmware development setup
2019-03-19 added basic modules
2019-03-22 added 3D models for most PCB parts
2019-03-25 added lvgl submodule
2019-04-12 removed bme and lvgl submodules
2019-05-14 mlcd working
2019-10-18 last commit before starting V2
2020-01-09 digikey_cs_v0
2020-01-21 added gitignore
2020-01-21 small updates
2020-01-30 commit before debugging; branching to order only the power supply section
2020-02-06 pulled up fault and EN to V_REG to fix startup bug
2020-02-06 replace lsm303 with bmx160
2020-02-07 hikebuddy 10 day optimized test psm board
2020-02-07 clean up
2020-02-07 cleand up old files
2020-02-07 fixed power, routed bmx160, changed and routed buttons; cs_v2_non_macrofab
2020-02-07 cs_v2_macrofab_sdc_version
2020-02-10 reassigned input-only pins
2020-02-20 export cam files
2020-02-21 rerouted traces close to milling; moved milling layer to dimension
2020-03-05 minor tweak
2020-03-05 changed sd card to Molex, added pcbway acknowledgement
2020-03-05 gerbers updated
2020-03-05 added bom.xlx
2020-03-20 added pullups to buttons, moved jst2 to make room for connector, removed test pads and joined EN to Vreg
2020-03-20 moved LCD and jst2 a little bit to fit everything
